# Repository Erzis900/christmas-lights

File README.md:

# christmas-lights
 Wi-Fi controlled LED strips

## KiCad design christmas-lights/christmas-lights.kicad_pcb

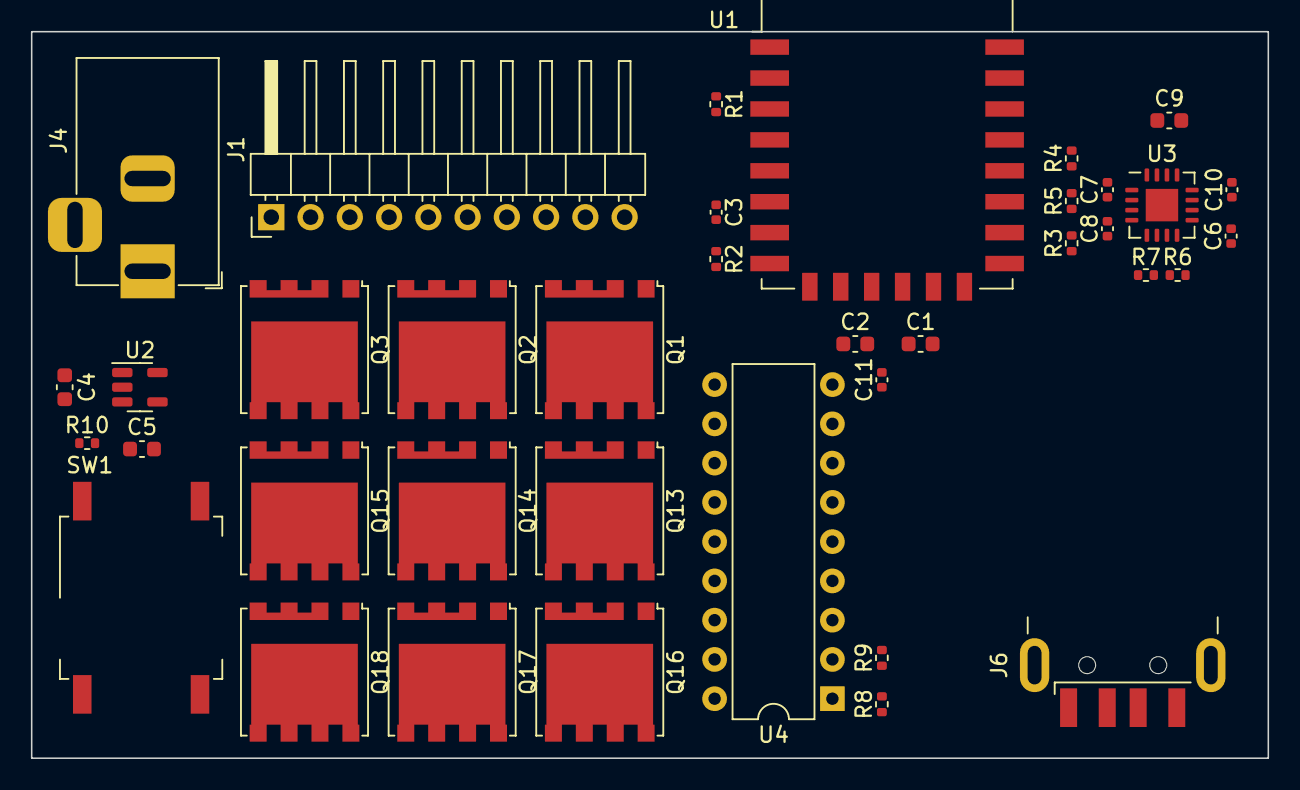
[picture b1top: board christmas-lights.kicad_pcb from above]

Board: 2 copper layers, 80.0 x 47.0 mm, 38 parts (0 on the bottom side), 36 nets, no tracks yet.

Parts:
C1: 1uF; C_0603_1608Metric
C2, C9: 4.7uF; C_0603_1608Metric
C3: 100nF; C_0402_1005Metric
C4, C5: 10uF; C_0603_1608Metric
C6, C10, C11: 0.1uF; C_0402_1005Metric
C7, C8: 47pF; C_0402_1005Metric
J1: Conn_01x10; PinHeader_1x10_P2.54mm_Horizontal
J4: Barrel_Jack_Switch; BarrelJack_Horizontal
J6: USB_A; USB_A_CNCTech_1001-011-01101_Horizontal
Q1, Q2, Q3, Q13, Q14, Q15, Q16, Q17, Q18: NMOS; PQFN_8x8
R1, R2, R3, R4, R5, R10: 10k; R_0402_1005Metric
R6, R7: 27R; R_0402_1005Metric
R8, R9: 1k tbd; R_0402_1005Metric
SW1: SW_MEC_5G; SW_MEC_5GSH9
U1: ESP-12E
U2: SPX3819M5-L-3-3; SOT-23-5
U3: FT230XQ; QFN-16-1EP_4x4mm_P0.65mm_EP2.1x2.1mm
U4: MCP23008-xP; DIP-18_W7.62mm

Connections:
+5V: C5.1, C11.2, J6.1 (VBUS), R8.1, R9.1, U2.1 (IN), U2.3 (EN), U4.18 (VDD)
+12V: J1.1, J4.1
/BLUE1: Q3.2 (G), U1.5 (GPIO14)
/BLUE2: Q15.2 (G), U4.12 (GP2)
/BLUE3: Q18.2 (G), U4.15 (GP5)
/D+: C8.1, J6.3 (D+), R7.1
/D-: C7.1, J6.2 (D-), R6.1
/GREEN1: Q2.2 (G), U1.7 (GPIO13)
/GREEN2: Q14.2 (G), U4.11 (GP1)
/GREEN3: Q17.2 (G), U4.14 (GP4)
/RED1: Q1.2 (G), U1.6 (GPIO12)
/RED2: Q13.2 (G), U4.10 (GP0)
/RED3: Q16.2 (G), U4.13 (GP3)
/RST: R10.2, SW1.1 (A), SW1.2 (A), U1.1 (~RST), U4.6 (~RESET)
/RX: U1.22 (GPIO1/TXD), U3.2 (RXD)
/SCL: R8.2, U1.20 (GPIO5), U4.1 (SCL)
/SDA: R9.2, U1.19 (GPIO4), U4.2 (SDA)
/TX: U1.21 (GPIO3/RXD), U3.15 (TXD)
GND: C1.2, C2.2, C3.2, C4.2, C5.2, C6.2, C7.2, C8.2, C9.2, C10.2, C11.1, J4.2, J6.4 (GND), J6.5 (Shield), Q1.3 (S), Q2.3 (S), Q3.3 (S), Q13.3 (S), Q14.3 (S), Q15.3 (S), Q16.3 (S), Q17.3 (S), Q18.3 (S), R2.1, R3.1, SW1.3 (B), SW1.4 (B), U1.15 (GND), U2.2 (GND), U3.3 (GND), U3.13 (GND), U3.17 (GND), U4.9 (VSS)
unnamed: J1.2, Q1.1 (D)
unnamed: J1.3, Q2.1 (D)
unnamed: J1.4, Q3.1 (D)
unnamed: J1.5, Q13.1 (D)
unnamed: J1.6, Q14.1 (D)
unnamed: J1.7, Q15.1 (D)
unnamed: J1.8, Q16.1 (D)
unnamed: J1.9, Q17.1 (D)
unnamed: J1.10, Q18.1 (D)
unnamed: R1.2, U1.3 (EN)
unnamed: R4.1, U1.18 (GPIO0)
unnamed: R5.1, U1.17 (GPIO2)
unnamed: R3.2, U1.16 (GPIO15)
unnamed: C6.1, U3.8 (3V3OUT), U3.9 (~RESET)
unnamed: R6.2, U3.7 (USBDM)
unnamed: R7.2, U3.6 (USBDP)
VDD: C1.1, C2.1, C3.1, C4.1, C9.1, C10.1, R1.1, R2.2, R4.2, R5.2, R10.1, U1.8 (VCC), U2.5 (OUT), U3.1 (VCCIO), U3.10 (VCC)

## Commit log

2023-11-07 init
2023-11-09 Added 3.3V DC Regulator Power Supply
2023-12-05 Schematic
2023-12-12 Added USB to UART interface
2023-12-19 Added port expander etc.
    Added:
    -port expander
    -reset switch
    -USB connector
    -more LED strips to the control circuit
2023-12-19 Modification on LED control
    -LED's arranged for user readability
2023-12-29 PCB and schematic adjustments
